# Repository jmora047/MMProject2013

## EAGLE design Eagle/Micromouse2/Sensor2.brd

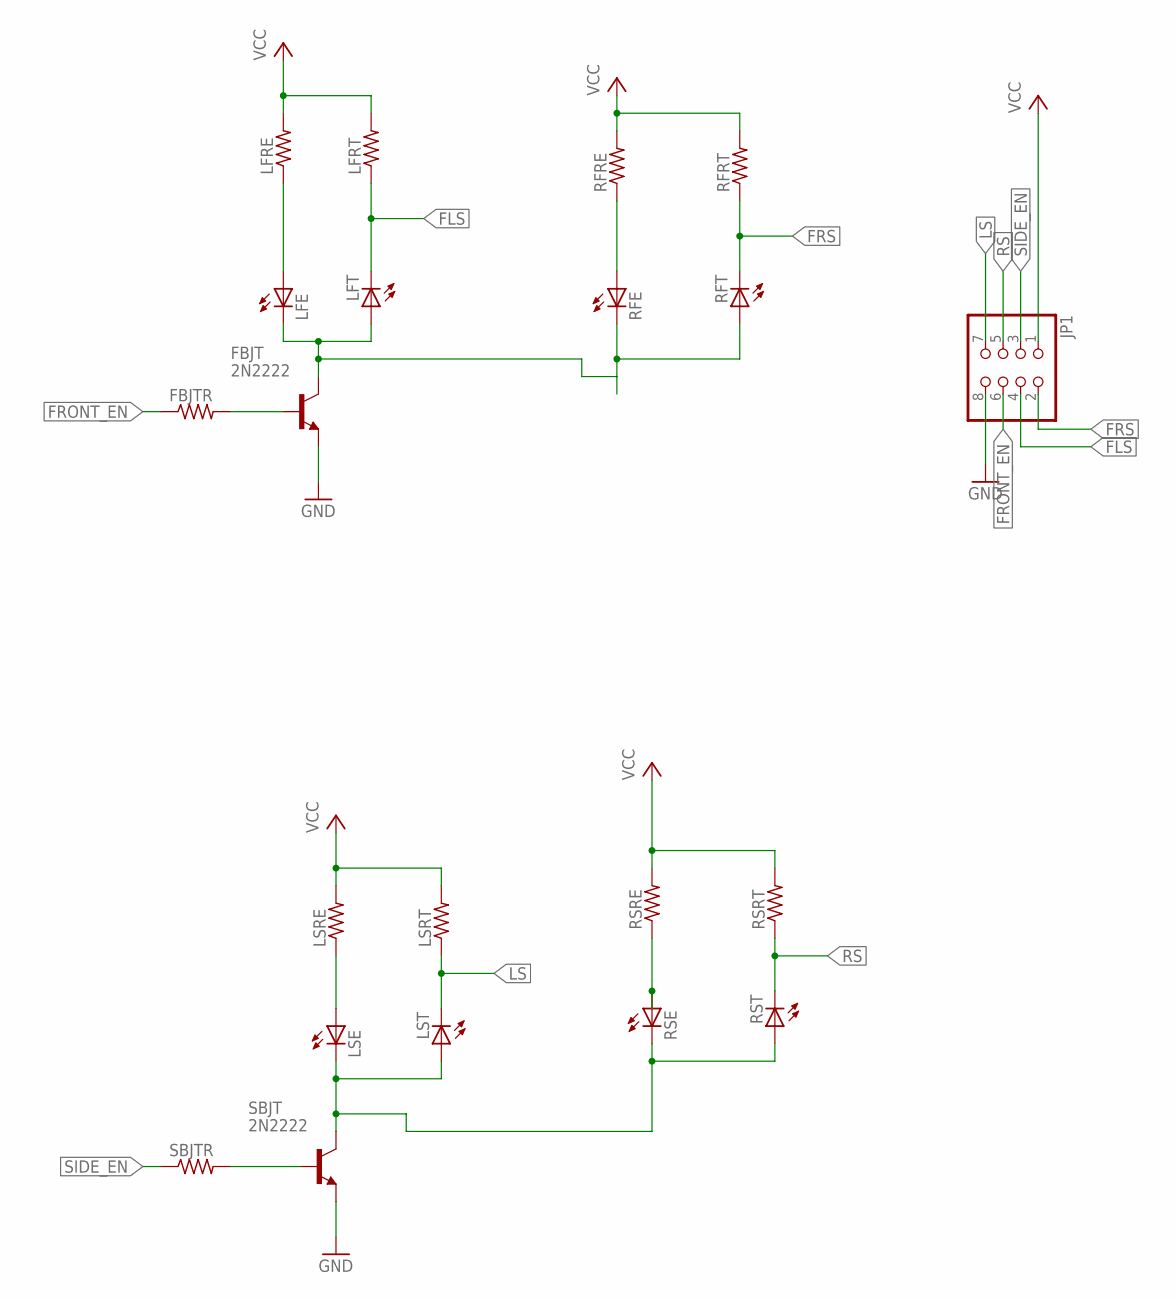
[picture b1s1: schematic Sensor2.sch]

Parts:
FBJT: 2N2222; TO92-EBC-OVAL
FBJTR: R-US_R0805; R0805
JP1: PINHD-2X4; 2X04
LFE: LED5MM
LFRE: R-US_R0805; R0805
LFRT: R-US_R0805; R0805
LFT: LED5MM
LSE: LED5MM
LSRE: R-US_R0805; R0805
LSRT: R-US_R0805; R0805
LST: LED5MM
RFE: LED5MM
RFRE: R-US_R0805; R0805
RFRT: R-US_R0805; R0805
RFT: LED5MM
RSE: LED5MM
RSRE: R-US_R0805; R0805
RSRT: R-US_R0805; R0805
RST: LED5MM
SBJT: 2N2222; TO92-EBC-OVAL
SBJTR: R-US_R0805; R0805

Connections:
FLS: JP1.4, LFRT.1, LFT.K (C)
FRONT_EN: FBJTR.1, JP1.6
FRS: JP1.2, RFRT.1, RFT.K (C)
GND: FBJT.E, JP1.8, SBJT.E
LS: JP1.7, LSRT.1, LST.K (C)
unnamed: LFE.A, LFRE.1
unnamed: FBJT.B, FBJTR.2
unnamed: FBJT.C, LFE.K (C), LFT.A, RFE.K (C), RFT.A
unnamed: SBJT.B, SBJTR.2
unnamed: LSE.K (C), LST.A, RSE.K (C), RST.A, SBJT.C
unnamed: RFE.A, RFRE.1
unnamed: LSE.A, LSRE.1
unnamed: RSE.A, RSRE.1
RS: JP1.5, RSRT.1, RST.K (C)
SIDE_EN: JP1.3, SBJTR.1
VCC: JP1.1, LFRE.2, LFRT.2, LSRE.2, LSRT.2, RFRE.2, RFRT.2, RSRE.2, RSRT.2

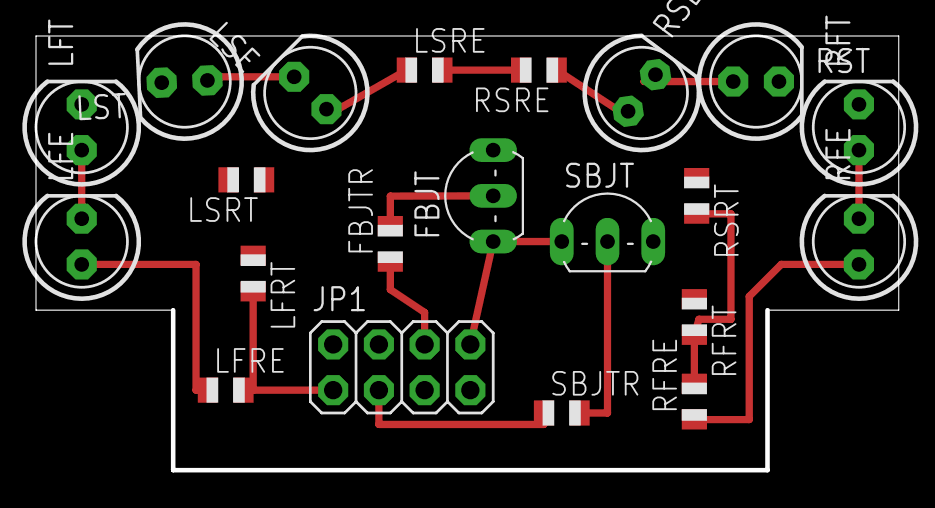
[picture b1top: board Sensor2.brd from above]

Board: 2 copper layers, 47.7 x 24.0 mm, 21 parts (0 on the bottom side), 16 nets.

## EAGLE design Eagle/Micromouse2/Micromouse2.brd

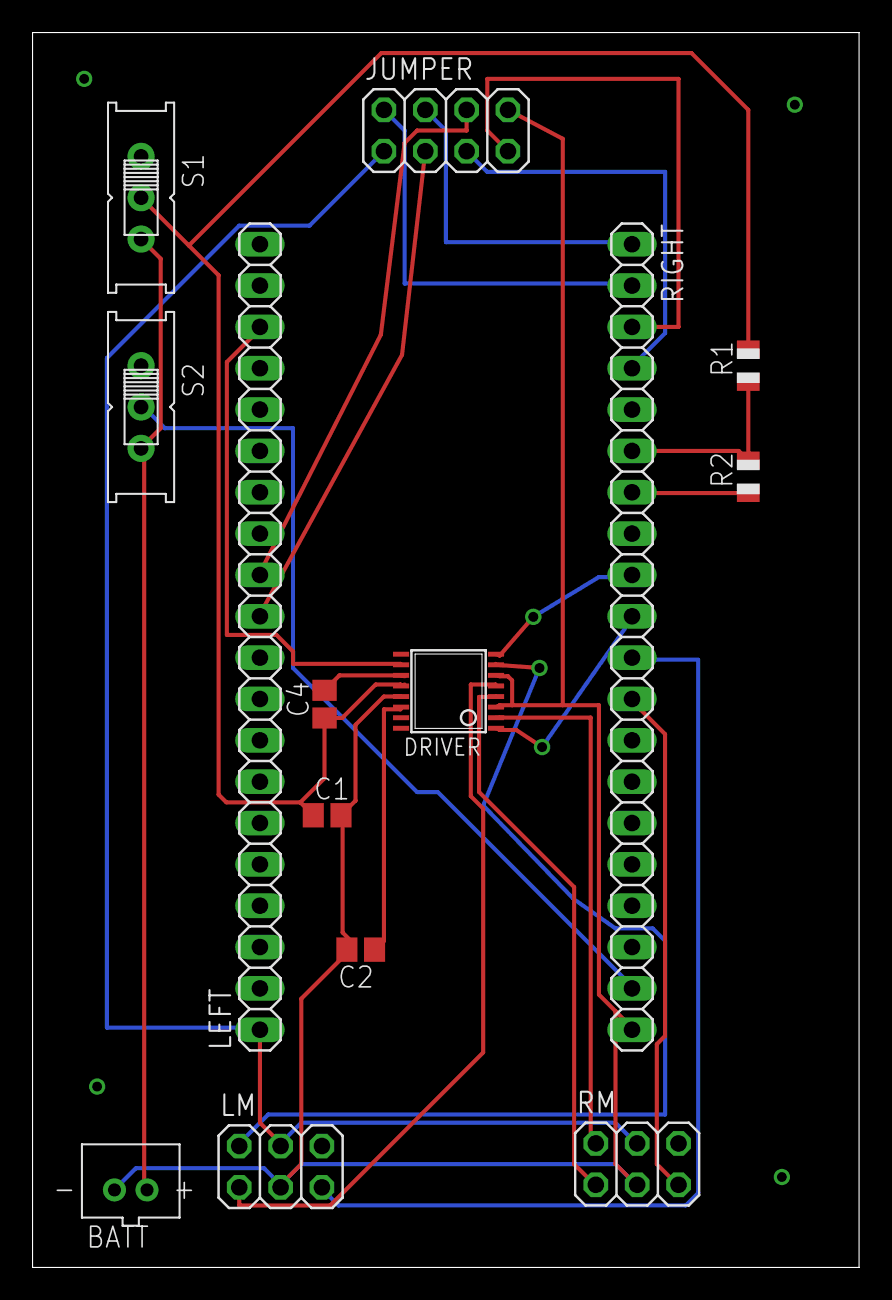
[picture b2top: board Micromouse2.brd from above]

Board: 2 copper layers, 50.8 x 75.9 mm, 14 parts (0 on the bottom side), 24 nets.

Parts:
BATT: JST-PH-2-THM
C1: 10uF; C0805
C2: 2.2uF; C0805
C4: .01uF; C0805
DRIVER: LMX2322; TSSOP16
JUMPER: 2X04
LEFT: 1X20
LM: 2X03
R1, R2: R0805
RIGHT: 1X20
RM: 2X03
S1, S2: EG1218

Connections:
+3V3: JUMPER.1, LEFT.1, LM.4, RM.4
B2IN: DRIVER.10, LEFT.18
BATT_CHECK: R1.1, R2.2, RIGHT.6
CHECK_EN: R2.1, RIGHT.7
FSENS_EN: JUMPER.6, LEFT.12
GND: BATT.2, C1.2, C2.2, DRIVER.3, DRIVER.6, DRIVER.13, JUMPER.8, LM.3, RIGHT.20, RM.3
LF_SENS: JUMPER.4, RIGHT.1
LS_SENS: JUMPER.7, RIGHT.3
unnamed: DRIVER.2, RM.2
unnamed: C2.1, DRIVER.14
unnamed: DRIVER.4, RM.1
unnamed: C4.2, DRIVER.11
unnamed: DRIVER.7, LM.2
unnamed: DRIVER.5, LM.1
unnamed: BATT.1, S1.S, S2.S
unnamed: DRIVER.8, RIGHT.9
unnamed: DRIVER.1, RIGHT.10
RF_SENS: JUMPER.2, RIGHT.2
RS_SENS: JUMPER.5, RIGHT.4
SSENS_EN: JUMPER.3, LEFT.11
TICK1: RIGHT.12, RM.5
TICK2: LM.5, RIGHT.11
VCC: C1.1, C4.1, DRIVER.12, R1.2, S1.P
VDD: RIGHT.19, S2.P

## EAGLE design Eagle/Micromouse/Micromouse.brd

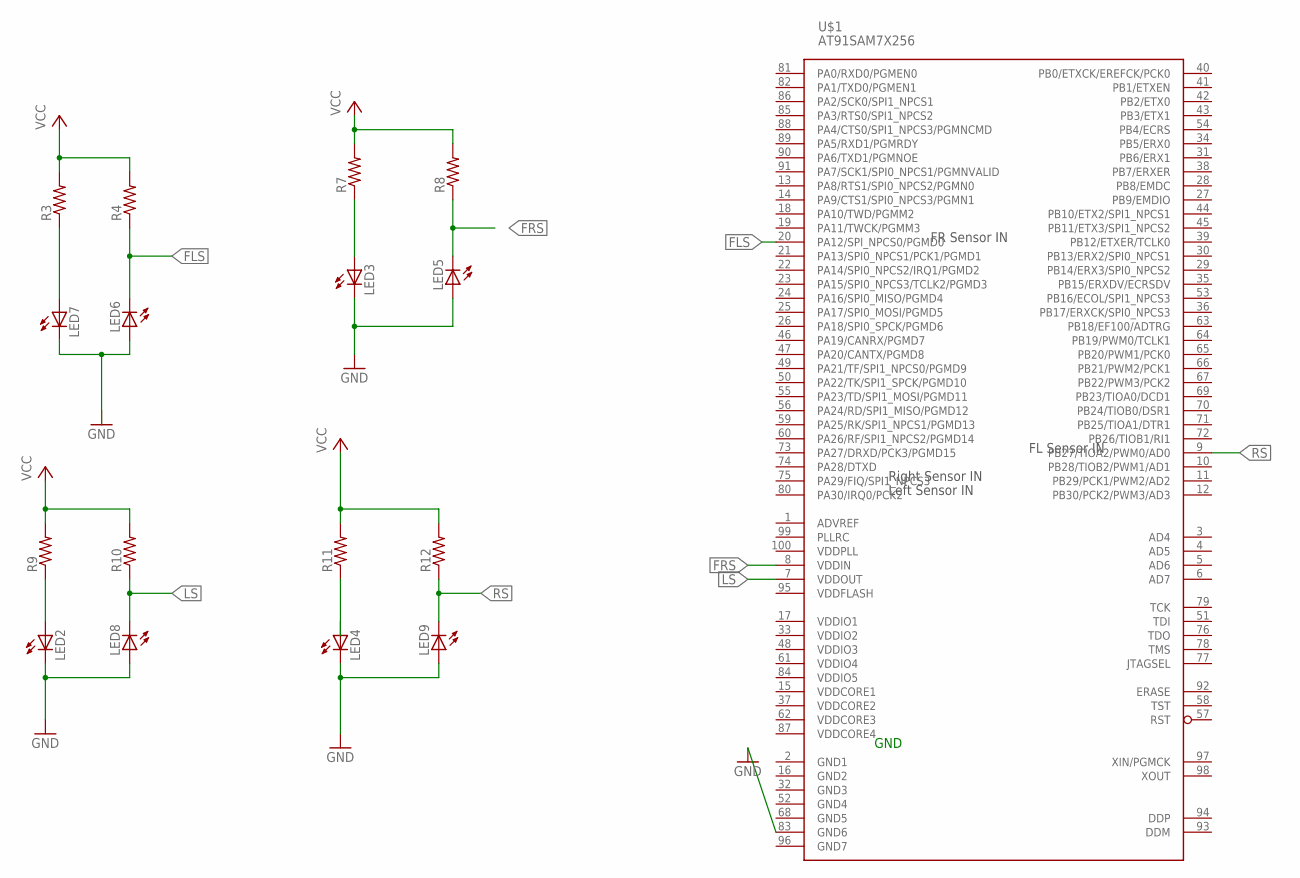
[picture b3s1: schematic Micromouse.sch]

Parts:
LED2, LED3, LED4, LED5, LED6, LED7, LED8, LED9: LED5MM
R3, R4, R7, R8, R9, R10, R11, R12: R-US_R0805; R0805
U$1: AT91SAM7X256; LQFP100

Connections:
FLS: LED6.K (C), R4.1, U$1.20 (PA12/SPI_NPCS0/PGMD0)
FRS: LED5.K (C), R8.1, U$1.8 (VDDIN)
GND: LED2.K (C), LED3.K (C), LED4.K (C), LED5.A, LED8.A, LED9.A, U$1.83 (GND6)
LS: LED8.K (C), R10.1, U$1.7 (VDDOUT)
unnamed: LED7.A, R3.1
unnamed: LED6.A, LED7.K (C)
unnamed: LED3.A, R7.1
unnamed: LED2.A, R9.1
RS: LED9.K (C), R12.1, U$1.9 (PB27/TIOA2/PWM0/AD0)
VCC: R3.2, R4.2, R7.2, R8.2, R9.2, R10.2, R11.2, R12.2

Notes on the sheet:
GND
Left Sensor IN
Right Sensor IN
FR Sensor IN
FL Sensor IN

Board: 2 copper layers, 17 parts (0 on the bottom side), 10 nets, no tracks yet.

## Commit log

2013-02-05 Added Libraries and project folder
2013-02-05 deleting files
2013-03-23 testing git
2013-03-23 Saying hi to you Andrew
2013-03-29 Andrews first commit
2013-05-18 pushing new schematic files. Located in Micrmouse2
2013-05-18 update schematic
2013-05-21 Updated Eagle Schematic
2013-05-24 Update to schematic2
2013-05-26 Added R1Tck which tells the mouse when to move and when to map during its first run. It will be controlled by mastertck assuming we get to a point where we expect to complete the maze. Also added a s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
2013-05-27 Now floodtck does not return an acknowledge flag until it is done executing
2013-05-28 Updating schematic and adding board
2013-05-29 Modified MovTck and added floats
2013-05-29 new schematics
2013-05-29 Sensor schematics
2013-05-30 updated eagle files for the sensor
